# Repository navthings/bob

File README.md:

bob

i saw a video of an led grid going up and down so fast it drew a floating cube in the air and i needed one. so this is bob, a mini volumetric display

what it is

a 4cm cube of light you can see from every side. a 16x16 board of blue leds goes up and down 40mm, 20 times a second, and at every height it lights up a different slice. your eyes cant keep up so all the slices blur into one 3d shape. the plan is a water sim inside it that sloshes around when you tilt bob. building for hack club fallen

how it works

a motor spins a scotch yoke that turns the spin into straight up and down motion. a hall sensor on the controller board sees a magnet once every turn so the esp32 knows exactly where the led board is. the esp32 shifts out one 16x16 slice at a time to the 16 driver chips on the led board, 16 slices per trip. the imu on the controller says which way is down, so the water falls the right way when you tilt it

whats in here

pcb/led-board/ is the led board (kicad). 256 leds, 16 tlc5926 drivers, 4 layers, 42x51mm
pcb/controller/ is the controller board (kicad). esp32-s3, usb-c for power and code, the motor driver, hall sensor, imu and a level shifter for the led board, 60x60mm
each board has a jlc/ folder with gerbers.zip, bom.csv and cpl.csv, just upload those to jlc
bom.csv is everything bob needs, both boards made and assembled at jlc plus the motor and mechanism bits (about $399 usd with shipping)
flip.py is the water sim on my mac (flip fluid), the one that goes on bob gets rewritten in c
code for bob comes when the boards do

led board

controller

schematics

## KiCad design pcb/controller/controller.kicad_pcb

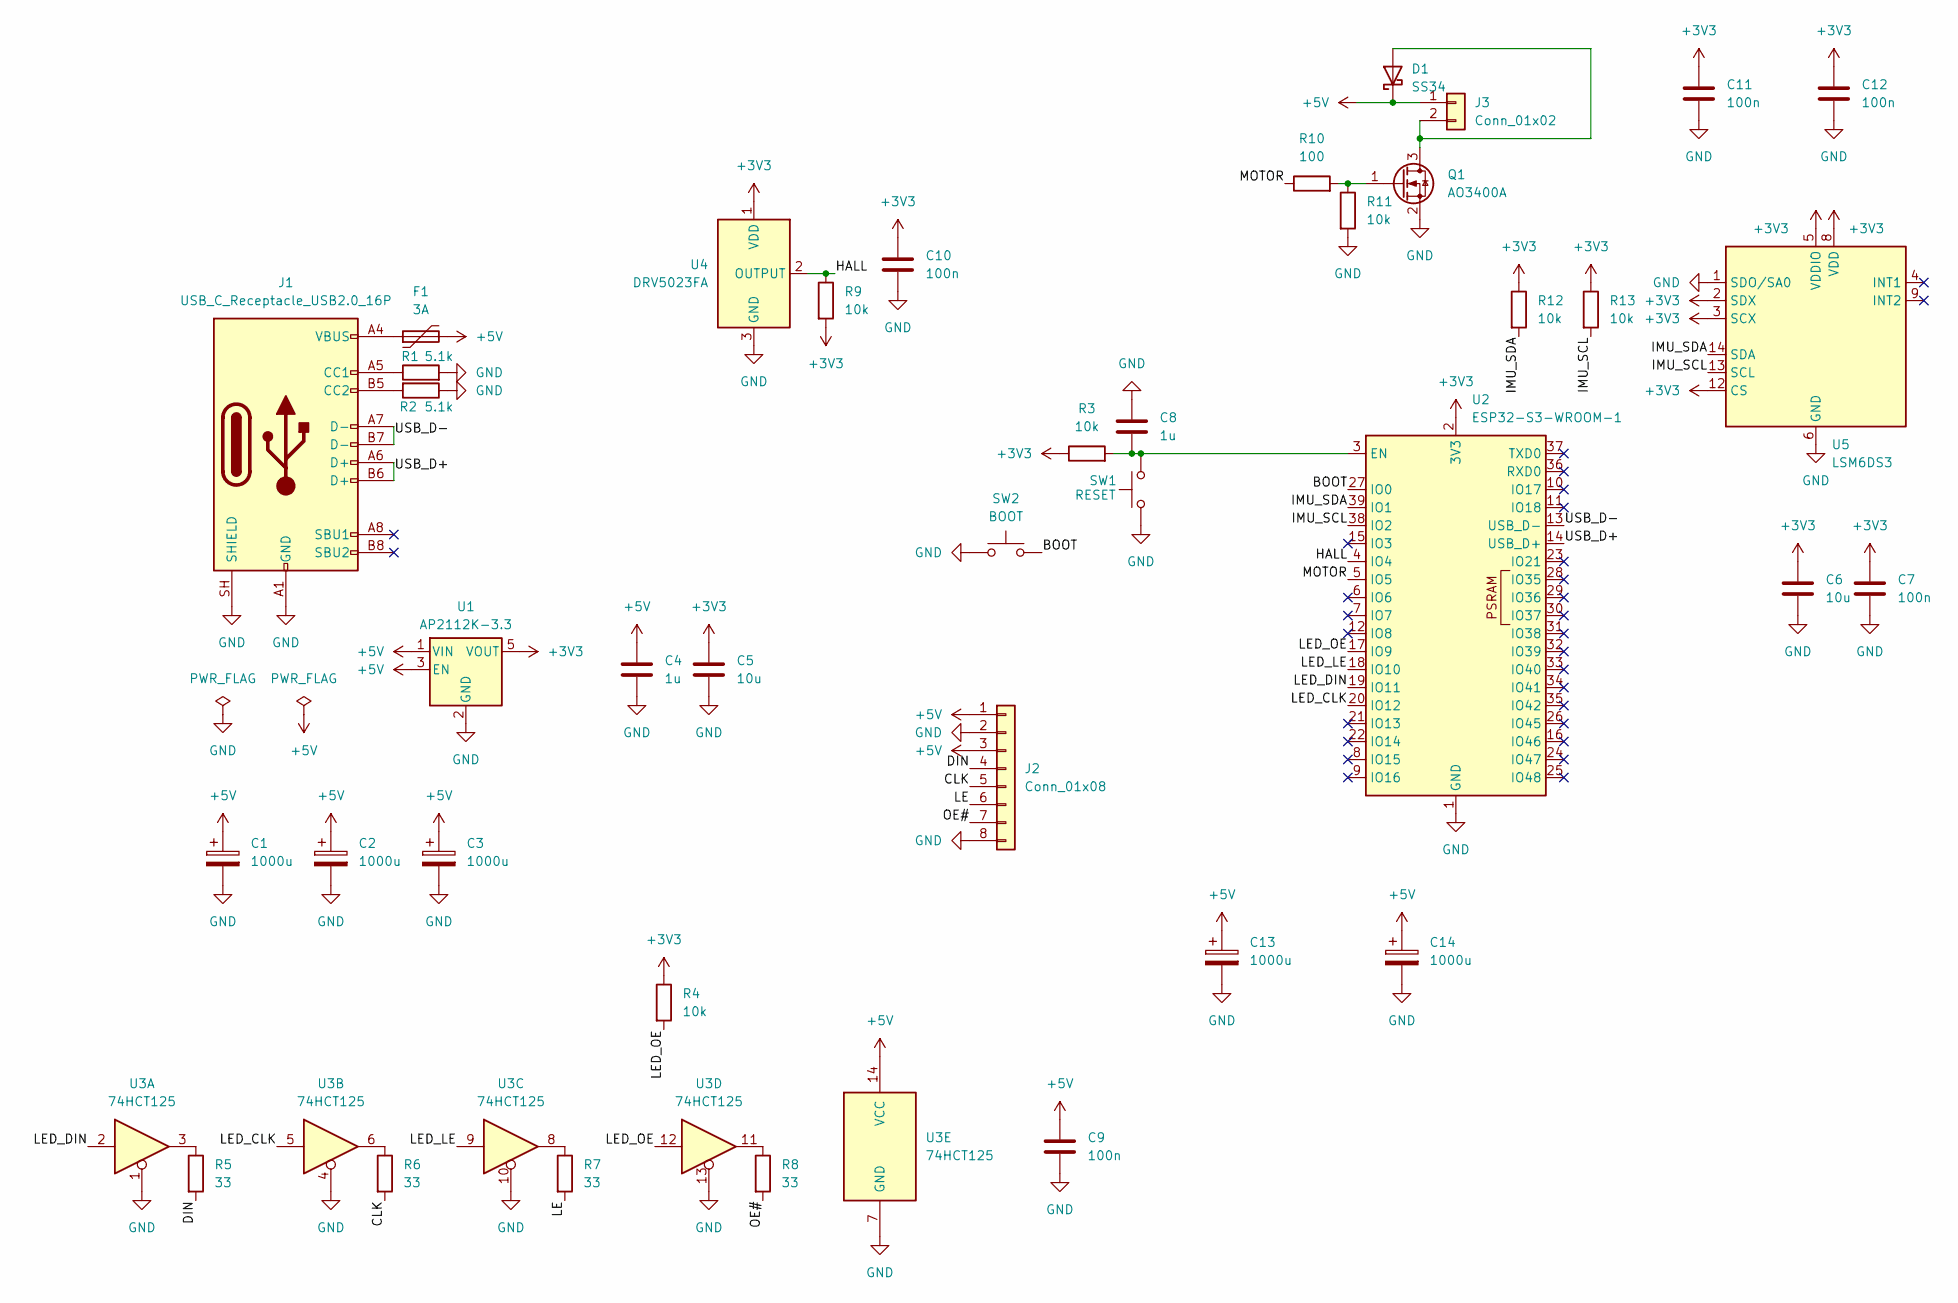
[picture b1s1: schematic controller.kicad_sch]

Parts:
C1, C2, C3, C13, C14: 1000u; CP_Elec_10x10.5
C4, C8: 1u; C_0603_1608Metric
C5, C6: 10u; C_0603_1608Metric
C7, C9, C10, C11, C12: 100n; C_0603_1608Metric
D1: SS34; D_SMA
F1: 3A; Fuse_1812_4532Metric
J1: USB_C_Receptacle_USB2.0_16P; USB_C_Receptacle_HRO_TYPE-C-31-M-12
J2: Conn_01x08; PinHeader_1x08_P2.54mm_Vertical
J3: Conn_01x02; JST_XH_B2B-XH-A_1x02_P2.50mm_Vertical
Q1: AO3400A; SOT-23
R1, R2: 5.1k; R_0603_1608Metric
R3, R4, R9, R11, R12, R13: 10k; R_0603_1608Metric
R5, R6, R7, R8: 33; R_0603_1608Metric
R10: 100; R_0603_1608Metric
SW1: RESET; SW_Push_1P1T_XKB_TS-1187A
SW2: BOOT; SW_Push_1P1T_XKB_TS-1187A
U1: AP2112K-3.3; SOT-23-5
U2: ESP32-S3-WROOM-1
U3: 74HCT125; SOIC-14_3.9x8.7mm_P1.27mm
U4: DRV5023FA; SOT-23
U5: LSM6DS3; LGA-14_3x2.5mm_P0.5mm_LayoutBorder3x4y

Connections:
+3V3: C5.1, C6.1, C7.1, C10.1, C11.1, C12.1, R3.1, R4.1, R9.2, R12.1, R13.1, U1.5 (VOUT), U2.2 (3V3), U4.1 (VDD), U5.2 (SDX), U5.3 (SCX), U5.5 (VDDIO), U5.8 (VDD), U5.12 (CS)
+5V: C1.1, C2.1, C3.1, C4.1, C9.1, C13.1, C14.1, D1.1 (K), F1.2, J2.1, J2.3, J3.1, U1.1 (VIN), U1.3 (EN), U3.14 (VCC)
/BOOT: SW2.2, U2.27 (IO0)
/CLK: J2.5, R6.2
/DIN: J2.4, R5.2
/HALL: R9.1, U2.4 (IO4), U4.2 (OUTPUT)
/IMU_SCL: R13.2, U2.38 (IO2), U5.13 (SCL)
/IMU_SDA: R12.2, U2.39 (IO1), U5.14 (SDA)
/LE: J2.6, R7.2
/LED_CLK: U2.20 (IO12), U3.5
/LED_DIN: U2.19 (IO11), U3.2
/LED_LE: U2.18 (IO10), U3.9
/LED_OE: R4.2, U2.17 (IO9), U3.12
/MOTOR: R10.1, U2.5 (IO5)
/OE#: J2.7, R8.2
/USB_D+: J1.A6 (D+), J1.B6 (D+), U2.14 (USB_D+)
/USB_D-: J1.A7 (D-), J1.B7 (D-), U2.13 (USB_D-)
GND: C1.2, C2.2, C3.2, C4.2, C5.2, C6.2, C7.2, C8.1, C9.2, C10.2, C11.2, C12.2, C13.2, C14.2, J1.A1 (GND), J1.A12 (GND), J1.B1 (GND), J1.B12 (GND), J1.SH (SHIELD), J2.2, J2.8, Q1.2 (S), R1.2, R2.1, R11.2, SW1.1, SW2.1, U1.2 (GND), U2.1 (GND), U2.40 (GND), U2.41 (GND), U3.1, U3.4, U3.7 (GND), U3.10, U3.13, U4.3 (GND), U5.1 (SDO/SA0), U5.6 (GND), U5.7 (GND)
unnamed: D1.2 (A), J3.2, Q1.3 (D)
unnamed: F1.1, J1.A4 (VBUS), J1.A9 (VBUS), J1.B4 (VBUS), J1.B9 (VBUS)
unnamed: J1.A5 (CC1), R1.1
unnamed: J1.B5 (CC2), R2.2
unnamed: Q1.1 (G), R10.2, R11.1
unnamed: R5.1, U3.3
unnamed: R6.1, U3.6
unnamed: R7.1, U3.8
unnamed: R8.1, U3.11
unnamed: C8.2, R3.2, SW1.2, U2.3 (EN)

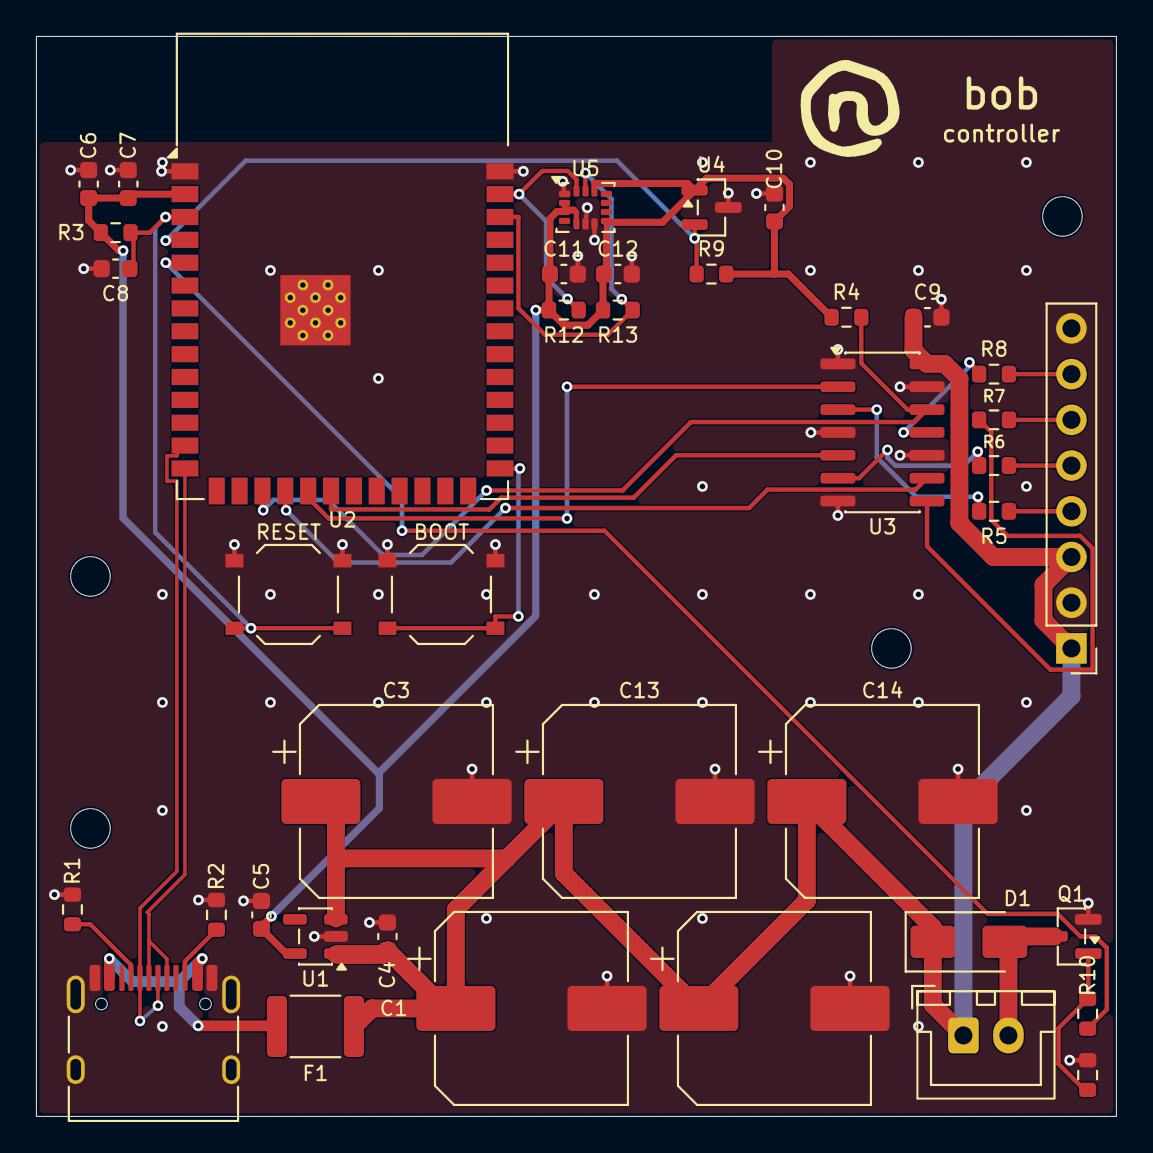
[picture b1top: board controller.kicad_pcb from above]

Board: 2 copper layers, 60.0 x 60.0 mm, 44 parts (0 on the bottom side), 28 nets.

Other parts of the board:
H1, H2, H3, H4: MountingHole_2.2mm_M2

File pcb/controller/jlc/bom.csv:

Comment,Designator,Footprint,LCSC Part #
1000u,"C1,C2,C3,C13,C14",CP_Elec_10x10.5,C3039783
1u,"C4,C8",C_0603_1608Metric,C15849
10u,"C5,C6",C_0603_1608Metric,C19702
100n,"C7,C9,C10,C11,C12",C_0603_1608Metric,C14663
SS34,D1,D_SMA,C8678
3A,F1,Fuse_1812_4532Metric,C2892442
USB_C_Receptacle_USB2.0_16P,J1,USB_C_Receptacle_HRO_TYPE-C-31-M-12,C165948
Conn_01x08,J2,PinHeader_1x08_P2.54mm_Vertical,C124381
Conn_01x02,J3,JST_XH_B2B-XH-A_1x02_P2.50mm_Vertical,C158012
AO3400A,Q1,SOT-23,C20917
5.1k,"R1,R2",R_0603_1608Metric,C23186
10k,"R3,R4,R9,R11,R12,R13",R_0603_1608Metric,C25804
33,"R5,R6,R7,R8",R_0603_1608Metric,C23140
100,R10,R_0603_1608Metric,C22775
TS-1187A,"SW1,SW2",SW_Push_1P1T_XKB_TS-1187A,C318884
AP2112K-3.3,U1,SOT-23-5,C51118
ESP32-S3-WROOM-1,U2,ESP32-S3-WROOM-1,C2913204
74HCT125,U3,SOIC-14_3.9x8.7mm_P1.27mm,C5962
DRV5023FA,U4,SOT-23,C114983
LSM6DS3,U5,LGA-14_3x2.5mm_P0.5mm_LayoutBorder3x4y,C967633

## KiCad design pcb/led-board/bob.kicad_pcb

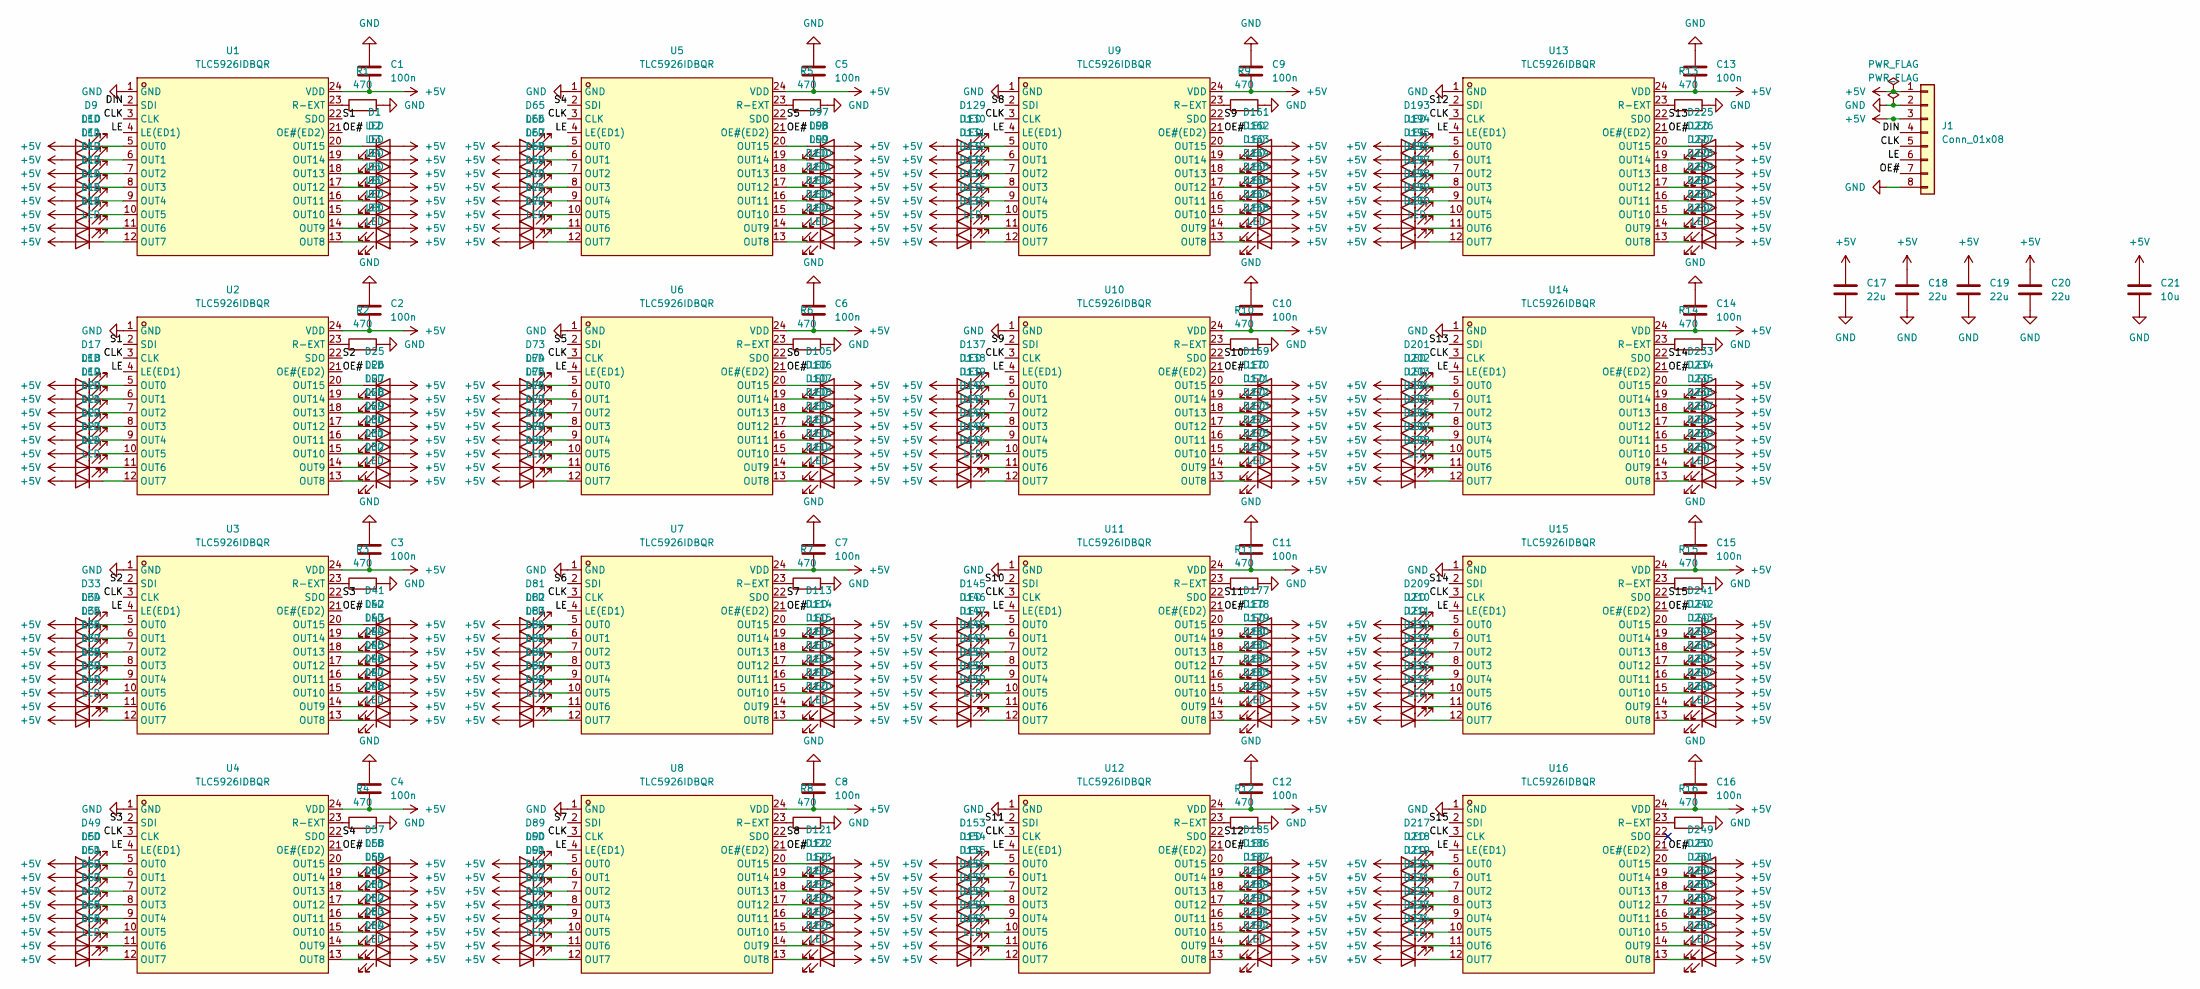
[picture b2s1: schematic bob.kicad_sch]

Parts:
C1, C2, C3, C4, C5, C6, C7, C8, C9, C10, C11, C12, C13, C14, C15, C16: 100n; C_0402_1005Metric; LCSC Part C1525
C17, C18, C19, C20: 22u; C_0805_2012Metric; LCSC Part C45783
C21: 10u; C_0805_2012Metric; LCSC Part C15850
D1, D2, D3, D4, D5, D6, D7, D8, D9, D10, D11, D12, D13, D14, D15, D16, D17, D18, D19, D20, D21, D22, D23, D24, D25, D26, D27, D28, D29, D30, D31, D32, D33, D34, D35, D36, D37, D38, D39, D40, D41, D42, D43, D44, D45, D46, D47, D48, D49, D50, D51, D52, D53, D54, D55, D56, D57, D58, D59, D60, D61, D62, D63, D64, D65, D66, D67, D68, D69, D70, D71, D72, D73, D74, D75, D76, D77, D78, D79, D80, D81, D82, D83, D84, D85, D86, D87, D88, D89, D90, D91, D92, D93, D94, D95, D96, D97, D98, D99, D100, D101, D102, D103, D104, D105, D106, D107, D108, D109, D110, D111, D112, D113, D114, D115, D116, D117, D118, D119, D120, D121, D122, D123, D124, D125, D126, D127, D128, D129, D130, D131, D132, D133, D134, D135, D136, D137, D138, D139, D140, D141, D142, D143, D144, D145, D146, D147, D148, D149, D150, D151, D152, D153, D154, D155, D156, D157, D158, D159, D160, D161, D162, D163, D164, D165, D166, D167, D168, D169, D170, D171, D172, D173, D174, D175, D176, D177, D178, D179, D180, D181, D182, D183, D184, D185, D186, D187, D188, D189, D190, D191, D192, D193, D194, D195, D196, D197, D198, D199, D200, D201, D202, D203, D204, D205, D206, D207, D208, D209, D210, D211, D212, D213, D214, D215, D216, D217, D218, D219, D220, D221, D222, D223, D224, D225, D226, D227, D228, D229, D230, D231, D232, D233, D234, D235, D236, D237, D238, D239, D240, D241, D242, D243, D244, D245, D246, D247, D248, D249, D250, D251, D252, D253, D254, D255, D256: LED; LED_0603_1608Metric; LCSC Part C434421
J1: Conn_01x08; PinHeader_1x08_P2.54mm_Vertical
R1, R2, R3, R4, R5, R6, R7, R8, R9, R10, R11, R12, R13, R14, R15, R16: 470; R_0402_1005Metric; LCSC Part C25117
U1, U2, U3, U4, U5, U6, U7, U8, U9, U10, U11, U12, U13, U14, U15, U16: TLC5926IDBQR; SSOP-24_L8.6-W3.9-P0.65-LS6.0-BL; MPN TLC5926IDBQR; LCSC Part C181595

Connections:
+5V: C1.2, C2.2, C3.2, C4.2, C5.2, C6.2, C7.2, C8.2, C9.2, C10.2, C11.2, C12.2, C13.2, C14.2, C15.2, C16.2, C17.1, C18.1, C19.1, C20.1, C21.1, D1.2 (A), D2.2 (A), D3.2 (A), D4.2 (A), D5.2 (A), D6.2 (A), D7.2 (A), D8.2 (A), D9.2 (A), D10.2 (A), D11.2 (A), D12.2 (A), D13.2 (A), D14.2 (A), D15.2 (A), D16.2 (A), D17.2 (A), D18.2 (A), D19.2 (A), D20.2 (A), D21.2 (A), D22.2 (A), D23.2 (A), D24.2 (A), D25.2 (A), D26.2 (A), D27.2 (A), D28.2 (A), D29.2 (A), D30.2 (A), D31.2 (A), D32.2 (A), D33.2 (A), D34.2 (A), D35.2 (A), D36.2 (A), D37.2 (A), D38.2 (A), D39.2 (A), D40.2 (A), D41.2 (A), D42.2 (A), D43.2 (A), D44.2 (A), D45.2 (A), D46.2 (A), D47.2 (A), D48.2 (A), D49.2 (A), D50.2 (A), D51.2 (A), D52.2 (A), D53.2 (A), D54.2 (A), D55.2 (A), D56.2 (A), D57.2 (A), D58.2 (A), D59.2 (A), D60.2 (A), D61.2 (A), D62.2 (A), D63.2 (A), D64.2 (A), D65.2 (A), D66.2 (A), D67.2 (A), D68.2 (A), D69.2 (A), D70.2 (A), D71.2 (A), D72.2 (A), D73.2 (A), D74.2 (A), D75.2 (A), D76.2 (A), D77.2 (A), D78.2 (A), D79.2 (A), D80.2 (A), D81.2 (A), D82.2 (A), D83.2 (A), D84.2 (A), D85.2 (A), D86.2 (A), D87.2 (A), D88.2 (A), D89.2 (A), D90.2 (A), D91.2 (A), D92.2 (A), D93.2 (A), D94.2 (A), D95.2 (A), D96.2 (A), D97.2 (A), D98.2 (A), D99.2 (A), D100.2 (A), D101.2 (A), D102.2 (A), D103.2 (A), D104.2 (A), D105.2 (A), D106.2 (A), D107.2 (A), D108.2 (A), D109.2 (A), D110.2 (A), D111.2 (A), D112.2 (A), D113.2 (A), D114.2 (A), D115.2 (A), D116.2 (A), D117.2 (A), D118.2 (A), D119.2 (A), D120.2 (A), D121.2 (A), D122.2 (A), D123.2 (A), D124.2 (A), D125.2 (A), D126.2 (A), D127.2 (A), D128.2 (A), D129.2 (A), D130.2 (A), D131.2 (A), D132.2 (A), D133.2 (A), D134.2 (A), D135.2 (A), D136.2 (A), D137.2 (A), D138.2 (A), D139.2 (A), D140.2 (A), D141.2 (A), D142.2 (A), D143.2 (A), D144.2 (A), D145.2 (A), D146.2 (A), D147.2 (A), D148.2 (A), D149.2 (A), D150.2 (A), D151.2 (A), D152.2 (A), D153.2 (A), D154.2 (A), D155.2 (A), D156.2 (A), D157.2 (A), D158.2 (A), D159.2 (A), D160.2 (A), D161.2 (A), D162.2 (A), D163.2 (A), D164.2 (A), D165.2 (A), D166.2 (A), D167.2 (A), D168.2 (A), D169.2 (A), D170.2 (A), D171.2 (A), D172.2 (A), D173.2 (A), D174.2 (A), D175.2 (A), D176.2 (A), D177.2 (A), D178.2 (A), D179.2 (A), D180.2 (A), D181.2 (A), D182.2 (A), D183.2 (A), D184.2 (A), D185.2 (A), D186.2 (A), D187.2 (A), D188.2 (A), D189.2 (A), D190.2 (A), D191.2 (A), D192.2 (A), D193.2 (A), D194.2 (A), D195.2 (A), D196.2 (A), D197.2 (A), D198.2 (A), D199.2 (A), D200.2 (A), D201.2 (A), D202.2 (A), D203.2 (A), D204.2 (A), D205.2 (A), D206.2 (A), D207.2 (A), D208.2 (A), D209.2 (A), D210.2 (A), D211.2 (A), D212.2 (A), D213.2 (A), D214.2 (A), D215.2 (A), D216.2 (A), D217.2 (A), D218.2 (A), D219.2 (A), D220.2 (A), D221.2 (A), D222.2 (A), D223.2 (A), D224.2 (A), D225.2 (A), D226.2 (A), D227.2 (A), D228.2 (A), D229.2 (A), D230.2 (A), D231.2 (A), D232.2 (A), D233.2 (A), D234.2 (A), D235.2 (A), D236.2 (A), D237.2 (A), D238.2 (A), D239.2 (A), D240.2 (A), D241.2 (A), D242.2 (A), D243.2 (A), D244.2 (A), D245.2 (A), D246.2 (A), D247.2 (A), D248.2 (A), D249.2 (A), D250.2 (A), D251.2 (A), D252.2 (A), D253.2 (A), D254.2 (A), D255.2 (A), D256.2 (A), J1.1, J1.3, U1.24 (VDD), U2.24 (VDD), U3.24 (VDD), U4.24 (VDD), U5.24 (VDD), U6.24 (VDD), U7.24 (VDD), U8.24 (VDD), U9.24 (VDD), U10.24 (VDD), U11.24 (VDD), U12.24 (VDD), U13.24 (VDD), U14.24 (VDD), U15.24 (VDD), U16.24 (VDD)
/CLK: J1.5, U1.3 (CLK), U2.3 (CLK), U3.3 (CLK), U4.3 (CLK), U5.3 (CLK), U6.3 (CLK), U7.3 (CLK), U8.3 (CLK), U9.3 (CLK), U10.3 (CLK), U11.3 (CLK), U12.3 (CLK), U13.3 (CLK), U14.3 (CLK), U15.3 (CLK), U16.3 (CLK)
/DIN: J1.4, U1.2 (SDI)
/LE: J1.6, U1.4 (LE(ED1)), U2.4 (LE(ED1)), U3.4 (LE(ED1)), U4.4 (LE(ED1)), U5.4 (LE(ED1)), U6.4 (LE(ED1)), U7.4 (LE(ED1)), U8.4 (LE(ED1)), U9.4 (LE(ED1)), U10.4 (LE(ED1)), U11.4 (LE(ED1)), U12.4 (LE(ED1)), U13.4 (LE(ED1)), U14.4 (LE(ED1)), U15.4 (LE(ED1)), U16.4 (LE(ED1))
/OE#: J1.7, U1.21 (OE#(ED2)), U2.21 (OE#(ED2)), U3.21 (OE#(ED2)), U4.21 (OE#(ED2)), U5.21 (OE#(ED2)), U6.21 (OE#(ED2)), U7.21 (OE#(ED2)), U8.21 (OE#(ED2)), U9.21 (OE#(ED2)), U10.21 (OE#(ED2)), U11.21 (OE#(ED2)), U12.21 (OE#(ED2)), U13.21 (OE#(ED2)), U14.21 (OE#(ED2)), U15.21 (OE#(ED2)), U16.21 (OE#(ED2))
/S1: U1.22 (SDO), U2.2 (SDI)
/S2: U2.22 (SDO), U3.2 (SDI)
/S3: U3.22 (SDO), U4.2 (SDI)
/S4: U4.22 (SDO), U5.2 (SDI)
/S5: U5.22 (SDO), U6.2 (SDI)
/S6: U6.22 (SDO), U7.2 (SDI)
/S7: U7.22 (SDO), U8.2 (SDI)
/S8: U8.22 (SDO), U9.2 (SDI)
/S9: U9.22 (SDO), U10.2 (SDI)
/S10: U10.22 (SDO), U11.2 (SDI)
/S11: U11.22 (SDO), U12.2 (SDI)
/S12: U12.22 (SDO), U13.2 (SDI)
/S13: U13.22 (SDO), U14.2 (SDI)
/S14: U14.22 (SDO), U15.2 (SDI)
/S15: U15.22 (SDO), U16.2 (SDI)
GND: C1.1, C2.1, C3.1, C4.1, C5.1, C6.1, C7.1, C8.1, C9.1, C10.1, C11.1, C12.1, C13.1, C14.1, C15.1, C16.1, C17.2, C18.2, C19.2, C20.2, C21.2, J1.2, J1.8, R1.2, R2.2, R3.2, R4.2, R5.2, R6.2, R7.2, R8.2, R9.2, R10.2, R11.2, R12.2, R13.2, R14.2, R15.2, R16.2, U1.1 (GND), U2.1 (GND), U3.1 (GND), U4.1 (GND), U5.1 (GND), U6.1 (GND), U7.1 (GND), U8.1 (GND), U9.1 (GND), U10.1 (GND), U11.1 (GND), U12.1 (GND), U13.1 (GND), U14.1 (GND), U15.1 (GND), U16.1 (GND)
unnamed: D1.1 (K), U1.20 (OUT15)
unnamed: D2.1 (K), U1.19 (OUT14)
unnamed: D3.1 (K), U1.18 (OUT13)
unnamed: D4.1 (K), U1.17 (OUT12)
unnamed: D5.1 (K), U1.16 (OUT11)
unnamed: D6.1 (K), U1.15 (OUT10)
unnamed: D7.1 (K), U1.14 (OUT9)
unnamed: D8.1 (K), U1.13 (OUT8)
unnamed: D9.1 (K), U1.5 (OUT0)
unnamed: D10.1 (K), U1.6 (OUT1)
unnamed: D11.1 (K), U1.7 (OUT2)
unnamed: D12.1 (K), U1.8 (OUT3)
unnamed: D13.1 (K), U1.9 (OUT4)
unnamed: D14.1 (K), U1.10 (OUT5)
unnamed: D15.1 (K), U1.11 (OUT6)
unnamed: D16.1 (K), U1.12 (OUT7)
unnamed: D17.1 (K), U2.5 (OUT0)
unnamed: D18.1 (K), U2.6 (OUT1)
unnamed: D19.1 (K), U2.7 (OUT2)
unnamed: D20.1 (K), U2.8 (OUT3)
unnamed: D21.1 (K), U2.9 (OUT4)
unnamed: D22.1 (K), U2.10 (OUT5)
unnamed: D23.1 (K), U2.11 (OUT6)
unnamed: D24.1 (K), U2.12 (OUT7)
unnamed: D25.1 (K), U2.20 (OUT15)
unnamed: D26.1 (K), U2.19 (OUT14)
unnamed: D27.1 (K), U2.18 (OUT13)
unnamed: D28.1 (K), U2.17 (OUT12)
unnamed: D29.1 (K), U2.16 (OUT11)
unnamed: D30.1 (K), U2.15 (OUT10)
unnamed: D31.1 (K), U2.14 (OUT9)
unnamed: D32.1 (K), U2.13 (OUT8)
unnamed: D33.1 (K), U3.5 (OUT0)
unnamed: D34.1 (K), U3.6 (OUT1)
unnamed: D35.1 (K), U3.7 (OUT2)
unnamed: D36.1 (K), U3.8 (OUT3)
unnamed: D37.1 (K), U3.9 (OUT4)
unnamed: D38.1 (K), U3.10 (OUT5)
unnamed: D39.1 (K), U3.11 (OUT6)
unnamed: D40.1 (K), U3.12 (OUT7)
unnamed: D41.1 (K), U3.20 (OUT15)
unnamed: D42.1 (K), U3.19 (OUT14)
unnamed: D43.1 (K), U3.18 (OUT13)
unnamed: D44.1 (K), U3.17 (OUT12)
unnamed: D45.1 (K), U3.16 (OUT11)
unnamed: D46.1 (K), U3.15 (OUT10)
unnamed: D47.1 (K), U3.14 (OUT9)
unnamed: D48.1 (K), U3.13 (OUT8)
unnamed: D49.1 (K), U4.5 (OUT0)
unnamed: D50.1 (K), U4.6 (OUT1)
unnamed: D51.1 (K), U4.7 (OUT2)
unnamed: D52.1 (K), U4.8 (OUT3)
unnamed: D53.1 (K), U4.9 (OUT4)
unnamed: D54.1 (K), U4.10 (OUT5)
unnamed: D55.1 (K), U4.11 (OUT6)
unnamed: D56.1 (K), U4.12 (OUT7)
unnamed: D57.1 (K), U4.20 (OUT15)
unnamed: D58.1 (K), U4.19 (OUT14)
unnamed: D59.1 (K), U4.18 (OUT13)
unnamed: D60.1 (K), U4.17 (OUT12)
unnamed: D61.1 (K), U4.16 (OUT11)
unnamed: D62.1 (K), U4.15 (OUT10)
unnamed: D63.1 (K), U4.14 (OUT9)
unnamed: D64.1 (K), U4.13 (OUT8)
unnamed: D65.1 (K), U5.5 (OUT0)
unnamed: D66.1 (K), U5.6 (OUT1)
unnamed: D67.1 (K), U5.7 (OUT2)
unnamed: D68.1 (K), U5.8 (OUT3)
unnamed: D69.1 (K), U5.9 (OUT4)
unnamed: D70.1 (K), U5.10 (OUT5)
unnamed: D71.1 (K), U5.11 (OUT6)
unnamed: D72.1 (K), U5.12 (OUT7)
unnamed: D73.1 (K), U6.5 (OUT0)
unnamed: D74.1 (K), U6.6 (OUT1)
unnamed: D75.1 (K), U6.7 (OUT2)
unnamed: D76.1 (K), U6.8 (OUT3)
unnamed: D77.1 (K), U6.9 (OUT4)
unnamed: D78.1 (K), U6.10 (OUT5)
unnamed: D79.1 (K), U6.11 (OUT6)
unnamed: D80.1 (K), U6.12 (OUT7)
unnamed: D81.1 (K), U7.5 (OUT0)
unnamed: D82.1 (K), U7.6 (OUT1)
unnamed: D83.1 (K), U7.7 (OUT2)
unnamed: D84.1 (K), U7.8 (OUT3)
unnamed: D85.1 (K), U7.9 (OUT4)
unnamed: D86.1 (K), U7.10 (OUT5)
unnamed: D87.1 (K), U7.11 (OUT6)
unnamed: D88.1 (K), U7.12 (OUT7)
unnamed: D89.1 (K), U8.5 (OUT0)
unnamed: D90.1 (K), U8.6 (OUT1)
unnamed: D91.1 (K), U8.7 (OUT2)
unnamed: D92.1 (K), U8.8 (OUT3)
unnamed: D93.1 (K), U8.9 (OUT4)
unnamed: D94.1 (K), U8.10 (OUT5)
unnamed: D95.1 (K), U8.11 (OUT6)
unnamed: D96.1 (K), U8.12 (OUT7)
unnamed: D97.1 (K), U5.20 (OUT15)
unnamed: D98.1 (K), U5.19 (OUT14)
unnamed: D99.1 (K), U5.18 (OUT13)
unnamed: D100.1 (K), U5.17 (OUT12)
unnamed: D101.1 (K), U5.16 (OUT11)
unnamed: D102.1 (K), U5.15 (OUT10)
unnamed: D103.1 (K), U5.14 (OUT9)
unnamed: D104.1 (K), U5.13 (OUT8)
unnamed: D105.1 (K), U6.20 (OUT15)
unnamed: D106.1 (K), U6.19 (OUT14)
unnamed: D107.1 (K), U6.18 (OUT13)
unnamed: D108.1 (K), U6.17 (OUT12)
unnamed: D109.1 (K), U6.16 (OUT11)
unnamed: D110.1 (K), U6.15 (OUT10)
unnamed: D111.1 (K), U6.14 (OUT9)
unnamed: D112.1 (K), U6.13 (OUT8)
unnamed: D113.1 (K), U7.20 (OUT15)
unnamed: D114.1 (K), U7.19 (OUT14)
unnamed: D115.1 (K), U7.18 (OUT13)
unnamed: D116.1 (K), U7.17 (OUT12)
unnamed: D117.1 (K), U7.16 (OUT11)
unnamed: D118.1 (K), U7.15 (OUT10)
unnamed: D119.1 (K), U7.14 (OUT9)
unnamed: D120.1 (K), U7.13 (OUT8)
unnamed: D121.1 (K), U8.20 (OUT15)
unnamed: D122.1 (K), U8.19 (OUT14)
unnamed: D123.1 (K), U8.18 (OUT13)
unnamed: D124.1 (K), U8.17 (OUT12)
unnamed: D125.1 (K), U8.16 (OUT11)
unnamed: D126.1 (K), U8.15 (OUT10)
unnamed: D127.1 (K), U8.14 (OUT9)
unnamed: D128.1 (K), U8.13 (OUT8)
unnamed: D129.1 (K), U9.5 (OUT0)
unnamed: D130.1 (K), U9.6 (OUT1)
unnamed: D131.1 (K), U9.7 (OUT2)
unnamed: D132.1 (K), U9.8 (OUT3)
unnamed: D133.1 (K), U9.9 (OUT4)
unnamed: D134.1 (K), U9.10 (OUT5)
unnamed: D135.1 (K), U9.11 (OUT6)
unnamed: D136.1 (K), U9.12 (OUT7)
unnamed: D137.1 (K), U10.5 (OUT0)
unnamed: D138.1 (K), U10.6 (OUT1)
unnamed: D139.1 (K), U10.7 (OUT2)
unnamed: D140.1 (K), U10.8 (OUT3)
unnamed: D141.1 (K), U10.9 (OUT4)
unnamed: D142.1 (K), U10.10 (OUT5)
unnamed: D143.1 (K), U10.11 (OUT6)
unnamed: D144.1 (K), U10.12 (OUT7)
unnamed: D145.1 (K), U11.5 (OUT0)
unnamed: D146.1 (K), U11.6 (OUT1)
unnamed: D147.1 (K), U11.7 (OUT2)
unnamed: D148.1 (K), U11.8 (OUT3)
unnamed: D149.1 (K), U11.9 (OUT4)
unnamed: D150.1 (K), U11.10 (OUT5)
unnamed: D151.1 (K), U11.11 (OUT6)
unnamed: D152.1 (K), U11.12 (OUT7)
unnamed: D153.1 (K), U12.5 (OUT0)
unnamed: D154.1 (K), U12.6 (OUT1)
unnamed: D155.1 (K), U12.7 (OUT2)
unnamed: D156.1 (K), U12.8 (OUT3)
unnamed: D157.1 (K), U12.9 (OUT4)
unnamed: D158.1 (K), U12.10 (OUT5)
unnamed: D159.1 (K), U12.11 (OUT6)
unnamed: D160.1 (K), U12.12 (OUT7)
unnamed: D161.1 (K), U9.20 (OUT15)
unnamed: D162.1 (K), U9.19 (OUT14)
unnamed: D163.1 (K), U9.18 (OUT13)
unnamed: D164.1 (K), U9.17 (OUT12)
unnamed: D165.1 (K), U9.16 (OUT11)
unnamed: D166.1 (K), U9.15 (OUT10)
unnamed: D167.1 (K), U9.14 (OUT9)
unnamed: D168.1 (K), U9.13 (OUT8)
unnamed: D169.1 (K), U10.20 (OUT15)
unnamed: D170.1 (K), U10.19 (OUT14)
unnamed: D171.1 (K), U10.18 (OUT13)
unnamed: D172.1 (K), U10.17 (OUT12)
unnamed: D173.1 (K), U10.16 (OUT11)
unnamed: D174.1 (K), U10.15 (OUT10)
unnamed: D175.1 (K), U10.14 (OUT9)
unnamed: D176.1 (K), U10.13 (OUT8)
unnamed: D177.1 (K), U11.20 (OUT15)
unnamed: D178.1 (K), U11.19 (OUT14)
unnamed: D179.1 (K), U11.18 (OUT13)
unnamed: D180.1 (K), U11.17 (OUT12)
unnamed: D181.1 (K), U11.16 (OUT11)
unnamed: D182.1 (K), U11.15 (OUT10)
unnamed: D183.1 (K), U11.14 (OUT9)
unnamed: D184.1 (K), U11.13 (OUT8)
unnamed: D185.1 (K), U12.20 (OUT15)
unnamed: D186.1 (K), U12.19 (OUT14)
unnamed: D187.1 (K), U12.18 (OUT13)
unnamed: D188.1 (K), U12.17 (OUT12)
unnamed: D189.1 (K), U12.16 (OUT11)
unnamed: D190.1 (K), U12.15 (OUT10)
unnamed: D191.1 (K), U12.14 (OUT9)
unnamed: D192.1 (K), U12.13 (OUT8)
unnamed: D193.1 (K), U13.5 (OUT0)
unnamed: D194.1 (K), U13.6 (OUT1)
unnamed: D195.1 (K), U13.7 (OUT2)
unnamed: D196.1 (K), U13.8 (OUT3)
unnamed: D197.1 (K), U13.9 (OUT4)
unnamed: D198.1 (K), U13.10 (OUT5)
unnamed: D199.1 (K), U13.11 (OUT6)
unnamed: D200.1 (K), U13.12 (OUT7)
unnamed: D201.1 (K), U14.5 (OUT0)
unnamed: D202.1 (K), U14.6 (OUT1)
unnamed: D203.1 (K), U14.7 (OUT2)
unnamed: D204.1 (K), U14.8 (OUT3)
unnamed: D205.1 (K), U14.9 (OUT4)
unnamed: D206.1 (K), U14.10 (OUT5)
unnamed: D207.1 (K), U14.11 (OUT6)
unnamed: D208.1 (K), U14.12 (OUT7)
unnamed: D209.1 (K), U15.5 (OUT0)
unnamed: D210.1 (K), U15.6 (OUT1)
unnamed: D211.1 (K), U15.7 (OUT2)
unnamed: D212.1 (K), U15.8 (OUT3)
unnamed: D213.1 (K), U15.9 (OUT4)
unnamed: D214.1 (K), U15.10 (OUT5)
unnamed: D215.1 (K), U15.11 (OUT6)
unnamed: D216.1 (K), U15.12 (OUT7)
unnamed: D217.1 (K), U16.5 (OUT0)
unnamed: D218.1 (K), U16.6 (OUT1)
unnamed: D219.1 (K), U16.7 (OUT2)
unnamed: D220.1 (K), U16.8 (OUT3)
unnamed: D221.1 (K), U16.9 (OUT4)
unnamed: D222.1 (K), U16.10 (OUT5)
unnamed: D223.1 (K), U16.11 (OUT6)
unnamed: D224.1 (K), U16.12 (OUT7)
unnamed: D225.1 (K), U13.20 (OUT15)
unnamed: D226.1 (K), U13.19 (OUT14)
unnamed: D227.1 (K), U13.18 (OUT13)
unnamed: D228.1 (K), U13.17 (OUT12)
unnamed: D229.1 (K), U13.16 (OUT11)
unnamed: D230.1 (K), U13.15 (OUT10)
unnamed: D231.1 (K), U13.14 (OUT9)
unnamed: D232.1 (K), U13.13 (OUT8)
unnamed: D233.1 (K), U14.20 (OUT15)
unnamed: D234.1 (K), U14.19 (OUT14)
unnamed: D235.1 (K), U14.18 (OUT13)
unnamed: D236.1 (K), U14.17 (OUT12)
unnamed: D237.1 (K), U14.16 (OUT11)
unnamed: D238.1 (K), U14.15 (OUT10)
unnamed: D239.1 (K), U14.14 (OUT9)
unnamed: D240.1 (K), U14.13 (OUT8)
unnamed: D241.1 (K), U15.20 (OUT15)
unnamed: D242.1 (K), U15.19 (OUT14)
unnamed: D243.1 (K), U15.18 (OUT13)
unnamed: D244.1 (K), U15.17 (OUT12)
unnamed: D245.1 (K), U15.16 (OUT11)
unnamed: D246.1 (K), U15.15 (OUT10)
unnamed: D247.1 (K), U15.14 (OUT9)
unnamed: D248.1 (K), U15.13 (OUT8)
unnamed: D249.1 (K), U16.20 (OUT15)
unnamed: D250.1 (K), U16.19 (OUT14)
unnamed: D251.1 (K), U16.18 (OUT13)
unnamed: D252.1 (K), U16.17 (OUT12)
unnamed: D253.1 (K), U16.16 (OUT11)
unnamed: D254.1 (K), U16.15 (OUT10)
unnamed: D255.1 (K), U16.14 (OUT9)
unnamed: D256.1 (K), U16.13 (OUT8)
unnamed: R1.1, U1.23 (R-EXT)
unnamed: R2.1, U2.23 (R-EXT)
unnamed: R3.1, U3.23 (R-EXT)
unnamed: R4.1, U4.23 (R-EXT)
unnamed: R5.1, U5.23 (R-EXT)
unnamed: R6.1, U6.23 (R-EXT)
unnamed: R7.1, U7.23 (R-EXT)
unnamed: R8.1, U8.23 (R-EXT)
unnamed: R9.1, U9.23 (R-EXT)
unnamed: R10.1, U10.23 (R-EXT)
unnamed: R11.1, U11.23 (R-EXT)
unnamed: R12.1, U12.23 (R-EXT)
unnamed: R13.1, U13.23 (R-EXT)
unnamed: R14.1, U14.23 (R-EXT)
unnamed: R15.1, U15.23 (R-EXT)
unnamed: R16.1, U16.23 (R-EXT)

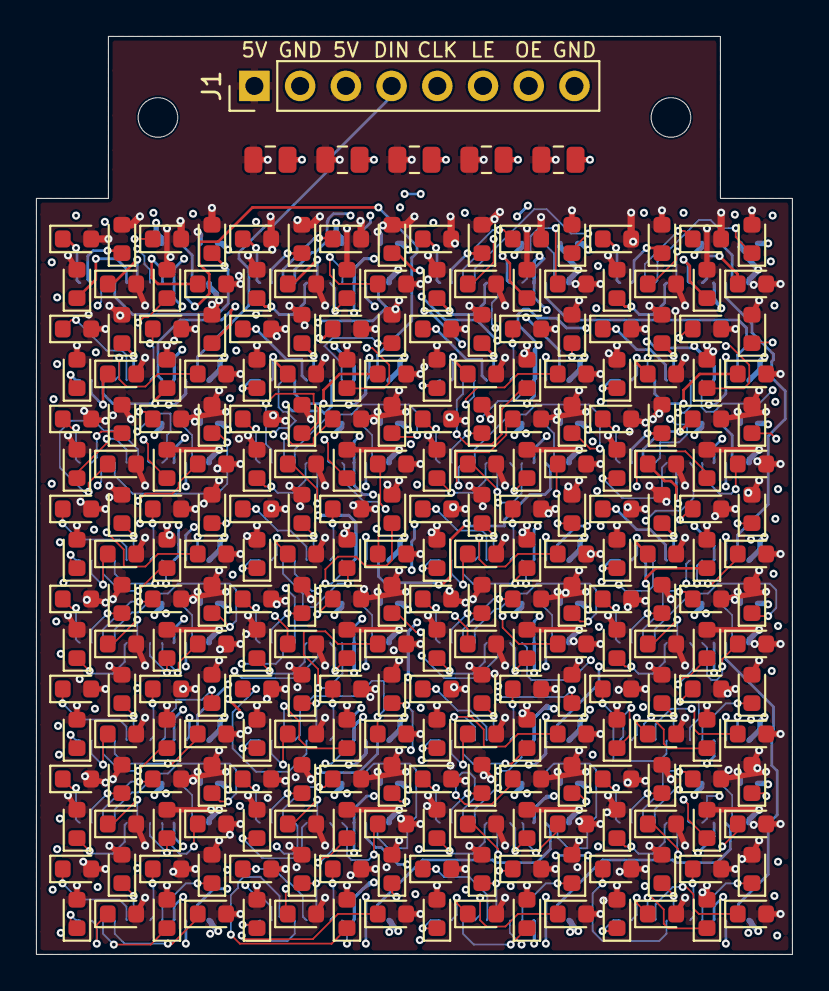
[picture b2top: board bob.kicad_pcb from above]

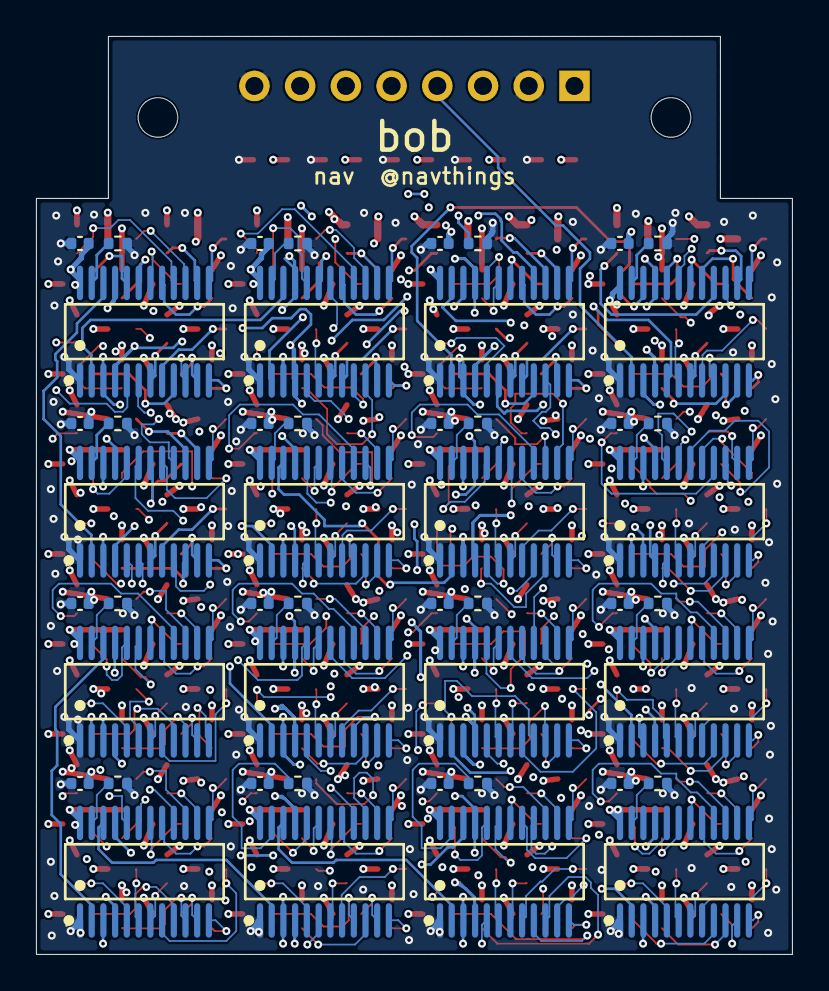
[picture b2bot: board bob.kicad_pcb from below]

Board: 4 copper layers, 42.0 x 51.0 mm, 312 parts (48 on the bottom side), 293 nets.

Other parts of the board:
H1, H2: MountingHole_2.2mm_M2

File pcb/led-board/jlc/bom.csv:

Comment,Designator,Footprint,LCSC Part #
100n,"C1,C2,C3,C4,C5,C6,C7,C8,C9,C10,C11,C12,C13,C14,C15,C16",C_0402_1005Metric,C1525
470,"R1,R2,R3,R4,R5,R6,R7,R8,R9,R10,R11,R12,R13,R14,R15,R16",R_0402_1005Metric,C25117
TLC5926IDBQR,"U1,U2,U3,U4,U5,U6,U7,U8,U9,U10,U11,U12,U13,U14,U15,U16",SSOP-24_L8.6-W3.9-P0.65-LS6.0-BL,C181595
22u,"C17,C18,C19,C20",C_0805_2012Metric,C45783
10u,C21,C_0805_2012Metric,C15850
LED,"D1,D2,D3,D4,D5,D6,D7,D8,D9,D10,D11,D12,D13,D14,D15,D16,D17,D18,D19,D20,D21,D22,D23,D24,D25,D26,D27,D28,D29,D30,D31,D32,D33,D34,D35,D36,D37,D38,D39,D40,D41,D42,D43,D44,D45,D46,D47,D48,D49,D50,D51,D52,D53,D54,D55,D56,D57,D58,D59,D60,D61,D62,D63,D64,D65,D66,D67,D68,D69,D70,D71,D72,D73,D74,D75,D76,D77,D78,D79,D80,D81,D82,D83,D84,D85,D86,D87,D88,D89,D90,D91,D92,D93,D94,D95,D96,D97,D98,D99,D100,D101,D102,D103,D104,D105,D106,D107,D108,D109,D110,D111,D112,D113,D114,D115,D116,D117,D118,D119,D120,D121,D122,D123,D124,D125,D126,D127,D128,D129,D130,D131,D132,D133,D134,D135,D136,D137,D138,D139,D140,D141,D142,D143,D144,D145,D146,D147,D148,D149,D150,D151,D152,D153,D154,D155,D156,D157,D158,D159,D160,D161,D162,D163,D164,D165,D166,D167,D168,D169,D170,D171,D172,D173,D174,D175,D176,D177,D178,D179,D180,D181,D182,D183,D184,D185,D186,D187,D188,D189,D190,D191,D192,D193,D194,D195,D196,D197,D198,D199,D200,D201,D202,D203,D204,D205,D206,D207,D208,D209,D210,D211,D212,D213,D214,D215,D216,D217,D218,D219,D220,D221,D222,D223,D224,D225,D226,D227,D228,D229,D230,D231,D232,D233,D234,D235,D236,D237,D238,D239,D240,D241,D242,D243,D244,D245,D246,D247,D248,D249,D250,D251,D252,D253,D254,D255,D256",LED_0603_1608Metric,C434421
Conn_01x08,J1,PinHeader_1x08_P2.54mm_Vertical,C124381
